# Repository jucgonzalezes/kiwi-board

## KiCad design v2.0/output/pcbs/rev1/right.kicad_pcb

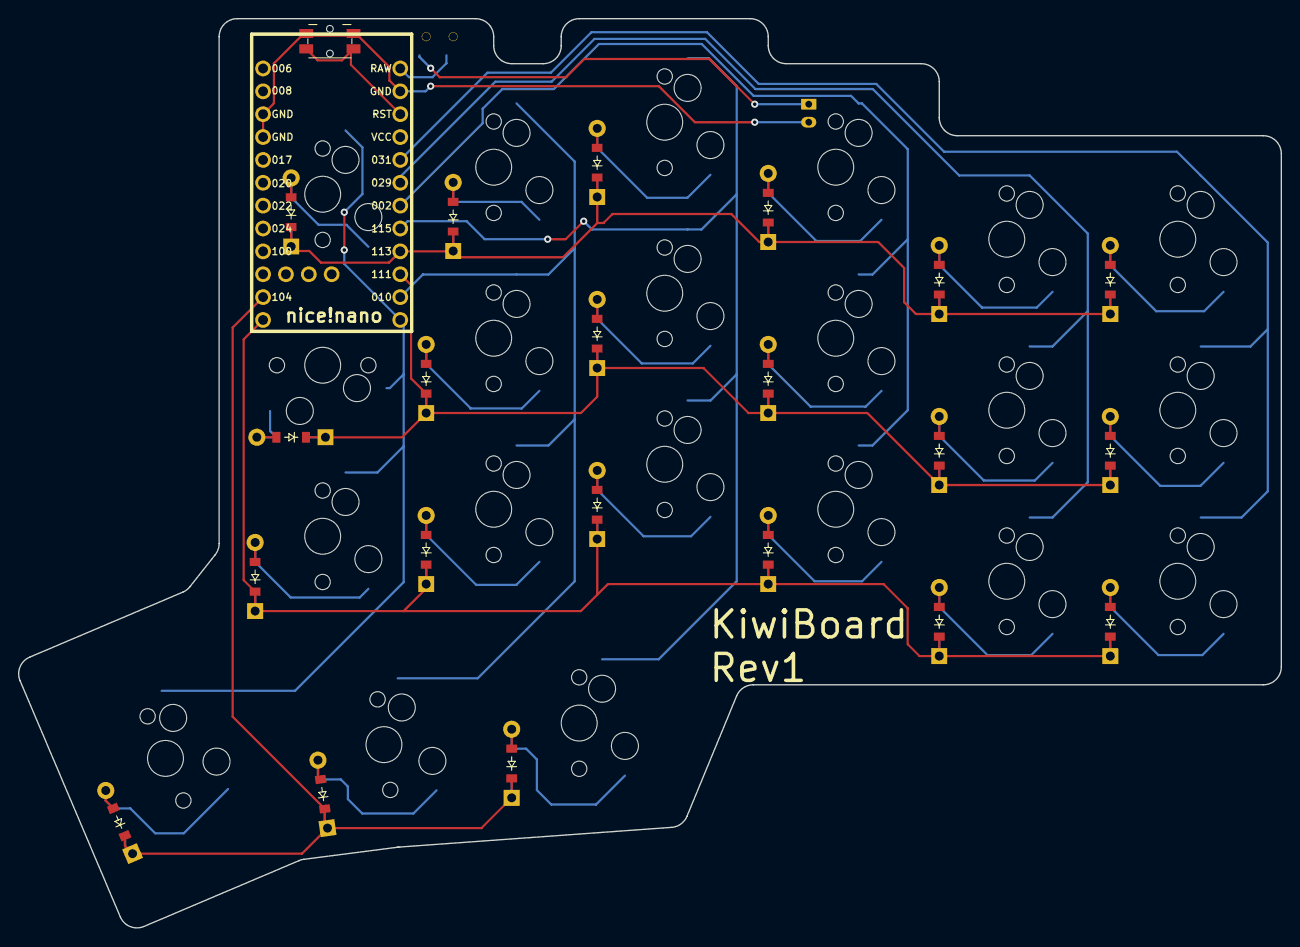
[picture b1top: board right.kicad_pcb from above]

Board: 2 copper layers, 140.3 x 101.0 mm, 46 parts (0 on the bottom side), 35 nets.

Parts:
B1: Panasonic_EVQPUL_EVQPUC
D1, D2, D3, D4, D5, D6, D7, D8, D9, D10, D11, D12, D13, D14, D15, D16, D17, D18, D19, D20, D21: ComboDiode
JST1: JST_PH_S2B-PH-K_02x2.00mm_Angled
MCU1: nice_nano
S1, S2, S3, S4, S5, S6, S7, S8, S9, S10, S11, S12, S13, S14, S15, S16, S17, S18, S19, S20, S21: MX
T1: SPDT_C128955

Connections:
GND: B1.1, JST1.2, MCU1.3, MCU1.4, MCU1.23
P002: MCU1.18, S7.1, S8.1, S9.1
P009: MCU1.13, S16.1, S17.1, S20.1, S21.1
P010: MCU1.14, S13.1, S14.1, S15.1, S19.1
P029: MCU1.19, S4.1, S5.1, S6.1
P031: MCU1.20, S1.1, S2.1, S3.1
P104: D15.1, D16.1, D17.1, MCU1.11
P106: D1.1, D4.1, D7.1, D10.1, D13.1, D14.1, MCU1.12
P111: D2.1, D5.1, D8.1, D11.1, D18.1, D21.1, MCU1.15
P113: D3.1, D6.1, D9.1, D12.1, D19.1, D20.1, MCU1.16
P115: MCU1.17, S10.1, S11.1, S12.1, S18.1
RAW: MCU1.24, T1.2
RST: B1.2, MCU1.22
mirror_ColA_Row1: D1.2, S1.2
mirror_ColA_Row2: D2.2, S2.2
mirror_ColA_Row3: D3.2, S3.2
mirror_ColB_Row1: D4.2, S4.2
mirror_ColB_Row2: D5.2, S5.2
mirror_ColB_Row3: D6.2, S6.2
mirror_ColC_Row1: D7.2, S7.2
mirror_ColC_Row2: D8.2, S8.2
mirror_ColC_Row3: D9.2, S9.2
mirror_ColD_Row0: D15.2, S18.2
mirror_ColD_Row1: D10.2, S10.2
mirror_ColD_Row2: D11.2, S11.2
mirror_ColD_Row3: D12.2, S12.2
mirror_ColE_Row0: D16.2, S19.2
mirror_ColE_Row1: D13.2, S13.2
mirror_ColE_Row2: D21.2, S14.2
mirror_ColE_Row3: D20.2, S15.2
mirror_ColF_Row0: D17.2, S20.2
mirror_ColF_Row1: D14.2, S16.2
mirror_ColF_Row2: D18.2, S21.2
mirror_ColF_Row3: D19.2, S17.2
pos: JST1.1, T1.1

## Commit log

2024-12-12 feature: add kiwi-board version 2
2024-12-12 feature: modify TR0;TC2 splay
2024-12-15 feature: finish left hand-side
2024-12-25 feature: complete v2.0. Ready for pre-prod
